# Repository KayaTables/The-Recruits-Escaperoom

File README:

Dit repository bevat de ontwerpfiles van de The Recruits escaperoom in Woerden (Bij HEL Shooter B.V.)

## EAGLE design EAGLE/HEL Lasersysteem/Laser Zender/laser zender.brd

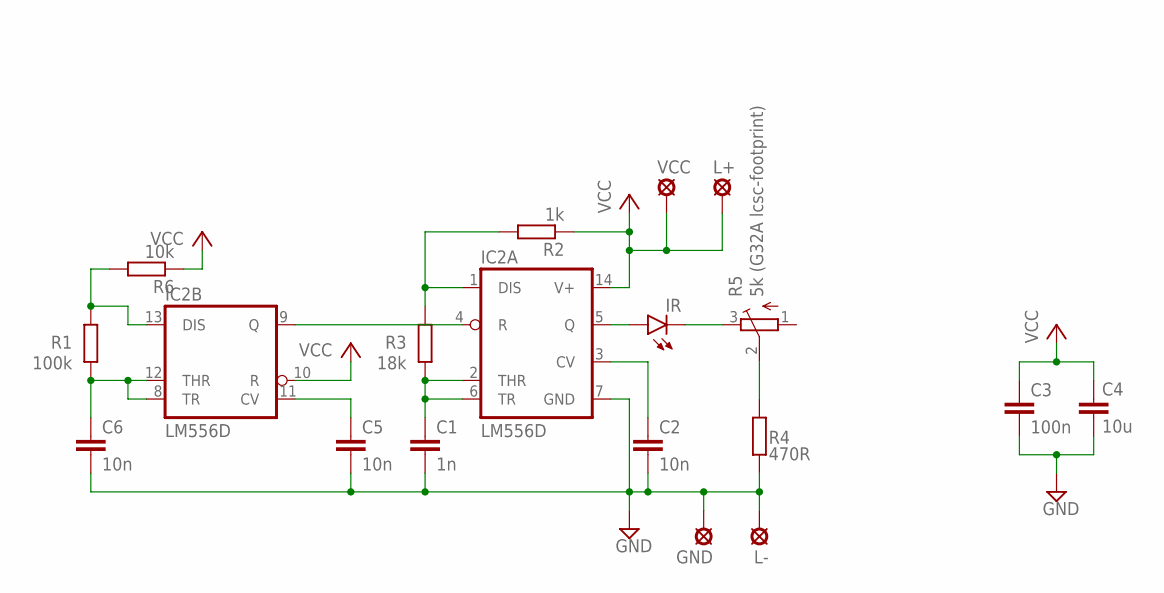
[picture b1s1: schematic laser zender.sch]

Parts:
C1: 1n; C0805
C2, C5, C6: 10n; C0805
C3: 100n; C0805
C4: 10u; C0805
GND: LSP10
IC2: LM556D; SO14
IR: LEDCHIPLED_0805; CHIPLED_0805
L+: LSP10
L-: LSP10
R1: 100k; R0805
R2: 1k; R0805
R3: 18k; R0805
R4: 470R; R0805
R5: 5k (G32A lcsc-footprint); 3223W
R6: 10k; R0805
VCC: LSP10

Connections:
GND: C1.2, C2.2, C3.2, C4.2, C5.2, C6.2, GND.MP, IC2.7 (GND), L-.MP, R4.2
unnamed: IR.C, R5.3 (E)
unnamed: C2.1, IC2.3 (CV)
unnamed: C1.1, IC2.2 (THR), IC2.6 (TR), R3.1
unnamed: R4.1, R5.2 (S)
unnamed: IC2.1 (DIS), R2.2, R3.2
unnamed: IC2.5 (Q), IR.A
unnamed: IC2.4 (R), IC2.9 (Q)
unnamed: IC2.13 (DIS), R1.2, R6.2
unnamed: C5.1, IC2.11 (CV)
unnamed: C6.1, IC2.8 (TR), IC2.12 (THR), R1.1
VCC: C3.1, C4.1, IC2.10 (R), IC2.14 (V+), L+.MP, R2.1, R6.1, VCC.MP

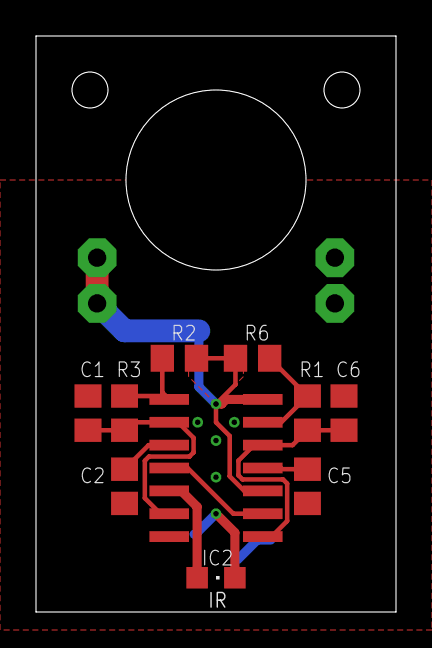
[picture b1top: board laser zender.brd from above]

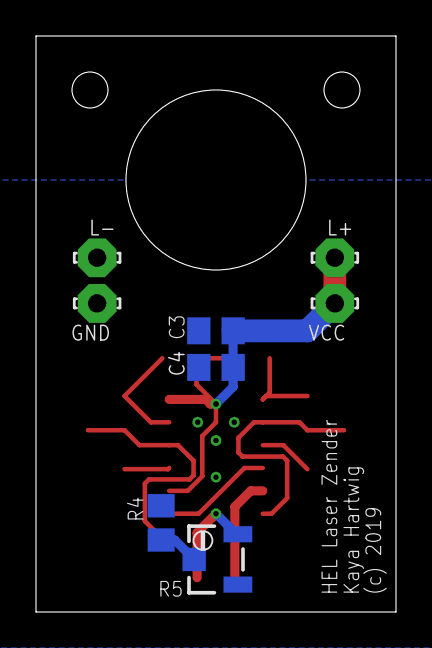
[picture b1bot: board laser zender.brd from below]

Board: 2 copper layers, 20.0 x 32.0 mm, 18 parts (8 on the bottom side), 12 nets.

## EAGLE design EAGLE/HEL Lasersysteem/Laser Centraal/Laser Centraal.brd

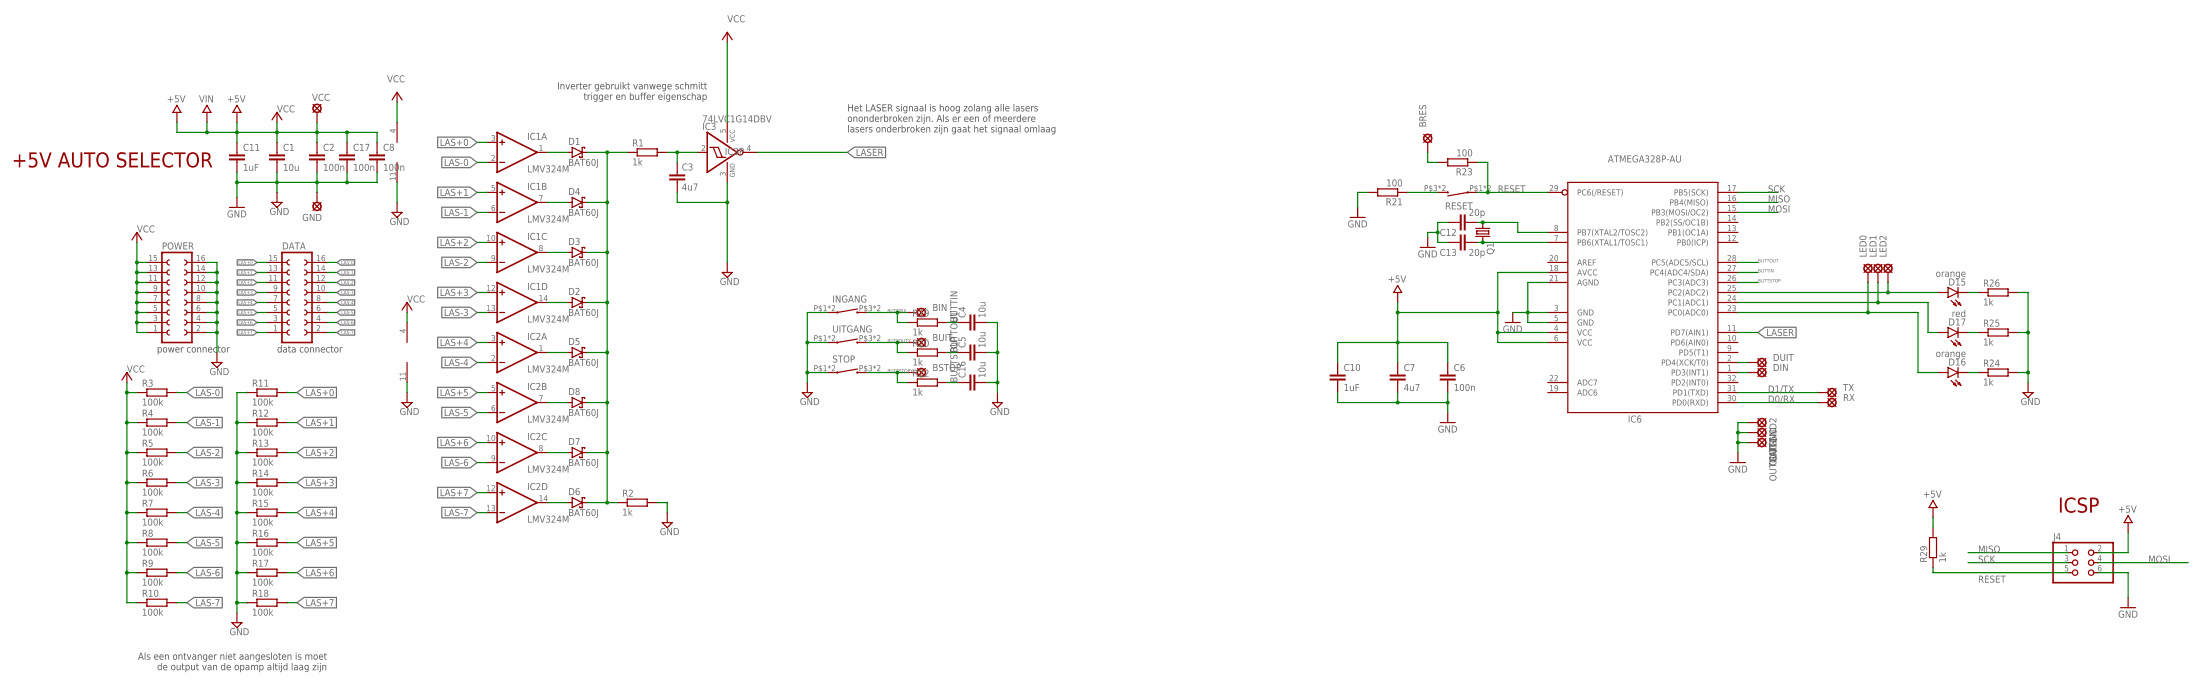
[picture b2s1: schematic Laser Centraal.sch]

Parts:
BIN: LSP10
BRES: LSP10
BSTOP: LSP10
BUIT: LSP10
C1, C4, C5, C16: 10u; C0805
C2, C6, C8, C17: 100n; C0805
C3, C7: 4u7; C0805
C10, C11: 1uF; C0805
C12, C13: 20p; C0805
D1, D2, D3, D4, D5, D6, D7, D8: BAT60J; SOD323_ST
D15, D16: orange; CHIP-LED0805
D17: red; CHIP-LED0805
DATA: FE08-2
DIN: LSP10
DUIT: LSP10
GND: LSP10
IC1, IC2: LMV324M; SO14
IC3: 74LVC1G14DBV; SOT23-5
IC6: ATMEGA328P-AU; TQFP32-08
INGANG: BRIGHTTSA061G100-250_SWITCH; BRIGHTTSA061G100-250
J4: 0114_PH254-203DF118A00V; 2X03
LED0, LED1, LED2: LSP10
OUTGND, OUTGND1, OUTGND2: LSP10
POWER: FE08-2
Q1: CRYSTALHC49U70; HC49U70
R1, R2, R19, R20, R22, R24, R25, R26, R29: 1k; R0805
R3, R4, R5, R6, R7, R8, R9, R10, R11, R12, R13, R14, R15, R16, R17, R18: 100k; R0805
R21, R23: 100; R0805
RESET: BRIGHTTSA061G100-250_SWITCH; BRIGHTTSA061G100-250
RX: LSP10
STOP: BRIGHTTSA061G100-250_SWITCH; BRIGHTTSA061G100-250
TX: LSP10
UITGANG: BRIGHTTSA061G100-250_SWITCH; BRIGHTTSA061G100-250
VCC: LSP10

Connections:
BUTTIN: C4.1, IC6.27 (PC4(ADC4/SDA)), R19.2
BUTTINX: BIN.MP, INGANG.P$3 (2), INGANG.P$4 (2), R19.1
BUTTOUT: C5.1, IC6.28 (PC5(ADC5/SCL)), R20.2
BUTTOUTX: BUIT.MP, R20.1, UITGANG.P$3 (2), UITGANG.P$4 (2)
BUTTSTOP: C16.1, IC6.26 (PC3(ADC3)), R22.2
BUTTSTOPX: BSTOP.MP, R22.1, STOP.P$3 (2), STOP.P$4 (2)
D0/RX: IC6.30 (PD0(RXD)), RX.MP
D1/TX: IC6.31 (PD1(TXD)), TX.MP
GND: C1.2, C2.2, C3.2, C4.2, C5.2, C6.2, C7.2, C8.2, C10.2, C11.2, C12.1, C13.1, C16.2, C17.2, GND.MP, IC1.11 (V-), IC2.11 (V-), IC3.3 (GND), IC6.3 (GND), IC6.5 (GND), IC6.21 (AGND), INGANG.P$1 (1), INGANG.P$2 (1), J4.6, OUTGND.MP, OUTGND1.MP, OUTGND2.MP, POWER.2, POWER.4, POWER.6, POWER.8, POWER.10, POWER.12, POWER.14, POWER.16, R2.2, R11.1, R12.1, R13.1, R14.1, R15.1, R16.1, R17.1, R18.1, R21.2, R24.2, R25.2, R26.2, STOP.P$1 (1), STOP.P$2 (1), UITGANG.P$1 (1), UITGANG.P$2 (1)
LAS+0: DATA.15, IC1.3 (+IN), R11.2
LAS+1: DATA.13, IC1.5 (+IN), R12.2
LAS+2: DATA.11, IC1.10 (+IN), R13.2
LAS+3: DATA.9, IC1.12 (+IN), R14.2
LAS+4: DATA.7, IC2.3 (+IN), R15.2
LAS+5: DATA.5, IC2.5 (+IN), R16.2
LAS+6: DATA.3, IC2.10 (+IN), R17.2
LAS+7: DATA.1, IC2.12 (+IN), R18.2
LAS-0: DATA.16, IC1.2 (-IN), R3.2
LAS-1: DATA.14, IC1.6 (-IN), R4.2
LAS-2: DATA.12, IC1.9 (-IN), R5.2
LAS-3: DATA.10, IC1.13 (-IN), R6.2
LAS-4: DATA.8, IC2.2 (-IN), R7.2
LAS-5: DATA.6, IC2.6 (-IN), R8.2
LAS-6: DATA.4, IC2.9 (-IN), R9.2
LAS-7: DATA.2, IC2.13 (-IN), R10.2
LASER: IC3.4 (O), IC6.11 (PD7(AIN1))
MISO: IC6.16 (PB4(MISO)), J4.1
MOSI: IC6.15 (PB3(MOSI/OC2)), J4.4
unnamed: D1.A, IC1.1 (OUT)
unnamed: D4.A, IC1.7 (OUT)
unnamed: D3.A, IC1.8 (OUT)
unnamed: D2.A, IC1.14 (OUT)
unnamed: D5.A, IC2.1 (OUT)
unnamed: D8.A, IC2.7 (OUT)
unnamed: D7.A, IC2.8 (OUT)
unnamed: D6.A, IC2.14 (OUT)
unnamed: D1.C, D2.C, D3.C, D4.C, D5.C, D6.C, D7.C, D8.C, R1.1, R2.1
unnamed: C3.1, IC3.2 (I), R1.2
unnamed: C13.2, IC6.7 (PB6(XTAL1/TOSC1)), Q1.2
unnamed: D16.C, R24.1
unnamed: D17.A, IC6.24 (PC1(ADC1)), LED1.MP
unnamed: D15.C, R26.1
unnamed: R21.1, RESET.P$3 (2), RESET.P$4 (2)
unnamed: D16.A, IC6.23 (PC0(ADC0)), LED0.MP
unnamed: C12.2, IC6.8 (PB7(XTAL2/TOSC2)), Q1.1
unnamed: BRES.MP, R23.2
unnamed: DUIT.MP, IC6.2 (PD4(XCK/T0))
unnamed: D17.C, R25.1
unnamed: D15.A, IC6.25 (PC2(ADC2)), LED2.MP
unnamed: DIN.MP, IC6.1 (PD3(INT1))
RESET: IC6.29 (PC6(/RESET)), J4.5, R23.1, R29.1, RESET.P$1 (1), RESET.P$2 (1)
SCK: IC6.17 (PB5(SCK)), J4.3
VCC: C1.1, C2.1, C6.1, C7.1, C8.1, C10.1, C11.1, C17.1, IC1.4 (V+), IC2.4 (V+), IC3.5 (VCC), IC6.4 (VCC), IC6.6 (VCC), IC6.18 (AVCC), J4.2, POWER.1, POWER.3, POWER.5, POWER.7, POWER.9, POWER.11, POWER.13, POWER.15, R3.1, R4.1, R5.1, R6.1, R7.1, R8.1, R9.1, R10.1, R29.2, VCC.MP

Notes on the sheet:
Inverter gebruikt vanwege schmitt trigger en buffer eigenschap
data connector
power connector
Als een ontvanger niet aangesloten is moet de output van de opamp altijd laag zijn
Het LASER signaal is hoog zolang alle lasers ononderbroken zijn. Als er een of meerdere lasers onderbroken zijn gaat het signaal omlaag
ICSP
+5V AUTO SELECTOR

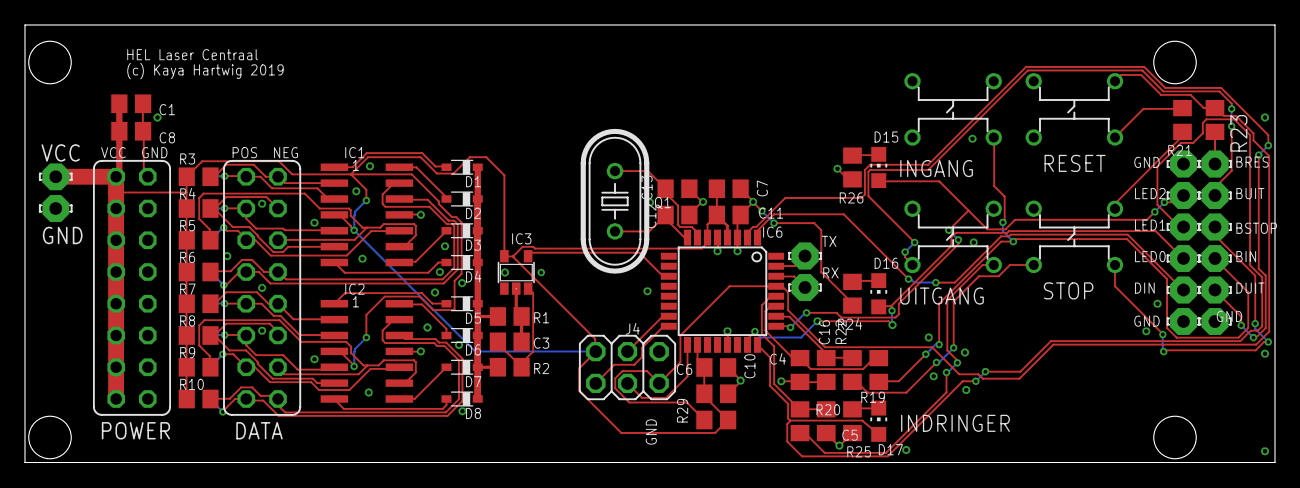
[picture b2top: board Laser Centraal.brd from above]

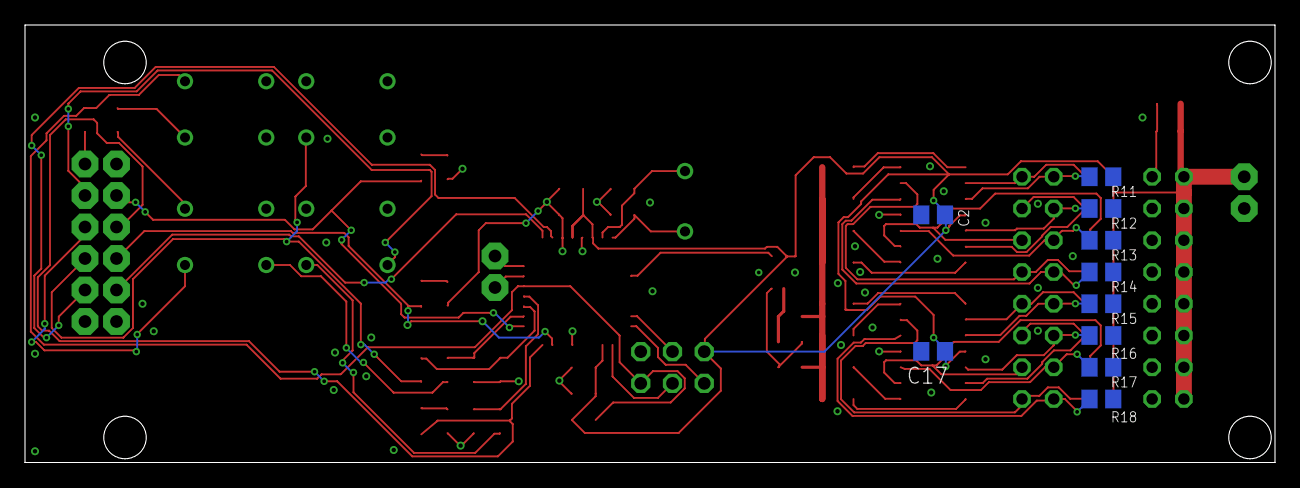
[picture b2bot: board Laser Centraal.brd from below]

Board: 2 copper layers, 100.0 x 35.0 mm, 80 parts (10 on the bottom side), 53 nets.

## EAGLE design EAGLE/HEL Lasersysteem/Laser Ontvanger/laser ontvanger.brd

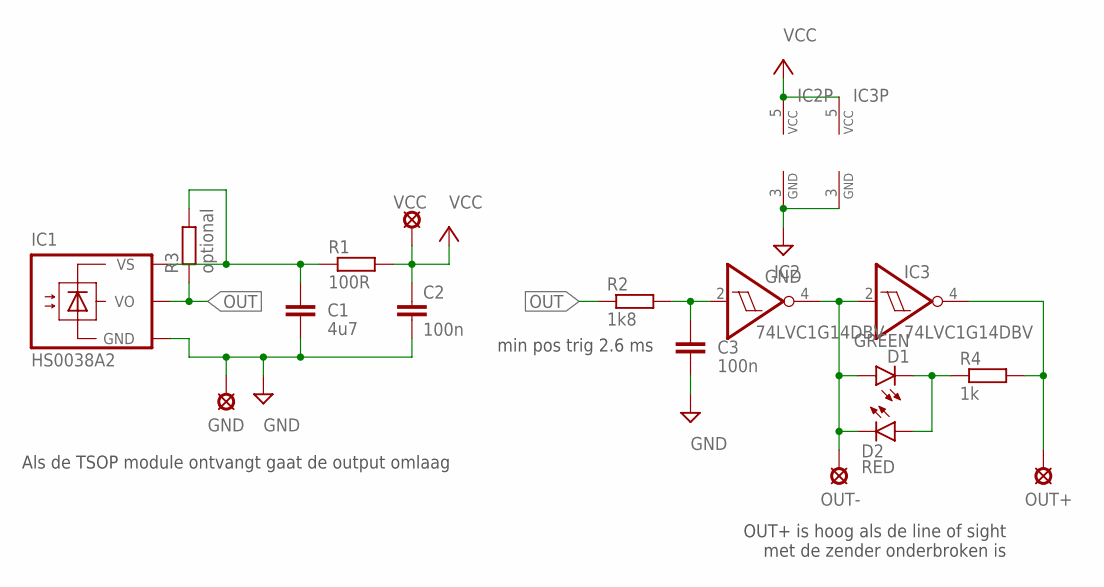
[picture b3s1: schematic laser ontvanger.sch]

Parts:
C1: 4u7; C0805
C2, C3: 100n; C0805
D1: GREEN; CHIP-LED0805
D2: RED; CHIP-LED0805
GND: LSP10
IC1: HS0038A2; TSOP17_TB1
IC2, IC3: 74LVC1G14DBV; SOT23-5
OUT+: LSP10
OUT-: LSP10
R1: 100R; R0805
R2: 1k8; R0805
R3: optional; R0805
R4: 1k; R0805
VCC: LSP10

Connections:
GND: C1.2, C2.2, C3.2, GND.MP, IC1.GND, IC2.3 (GND), IC3.3 (GND)
unnamed: C3.1, IC2.2 (I), R2.2
unnamed: D1.C, D2.A, R4.1
unnamed: D1.A, D2.C, IC2.4 (O), IC3.2 (I), OUT-.MP
unnamed: IC3.4 (O), OUT+.MP, R4.2
unnamed: C1.1, IC1.VS, R1.1, R3.2
OUT: IC1.VO, R2.1, R3.1
VCC: C2.1, IC2.5 (VCC), IC3.5 (VCC), R1.2, VCC.MP

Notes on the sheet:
Als de TSOP module ontvangt gaat de output omlaag
min pos trig 2.6 ms
OUT+ is hoog als de line of sight met de zender onderbroken is

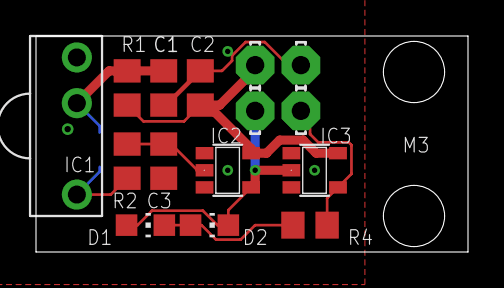
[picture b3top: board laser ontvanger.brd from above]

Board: 2 copper layers, 24.0 x 12.0 mm, 16 parts (1 on the bottom side), 8 nets.

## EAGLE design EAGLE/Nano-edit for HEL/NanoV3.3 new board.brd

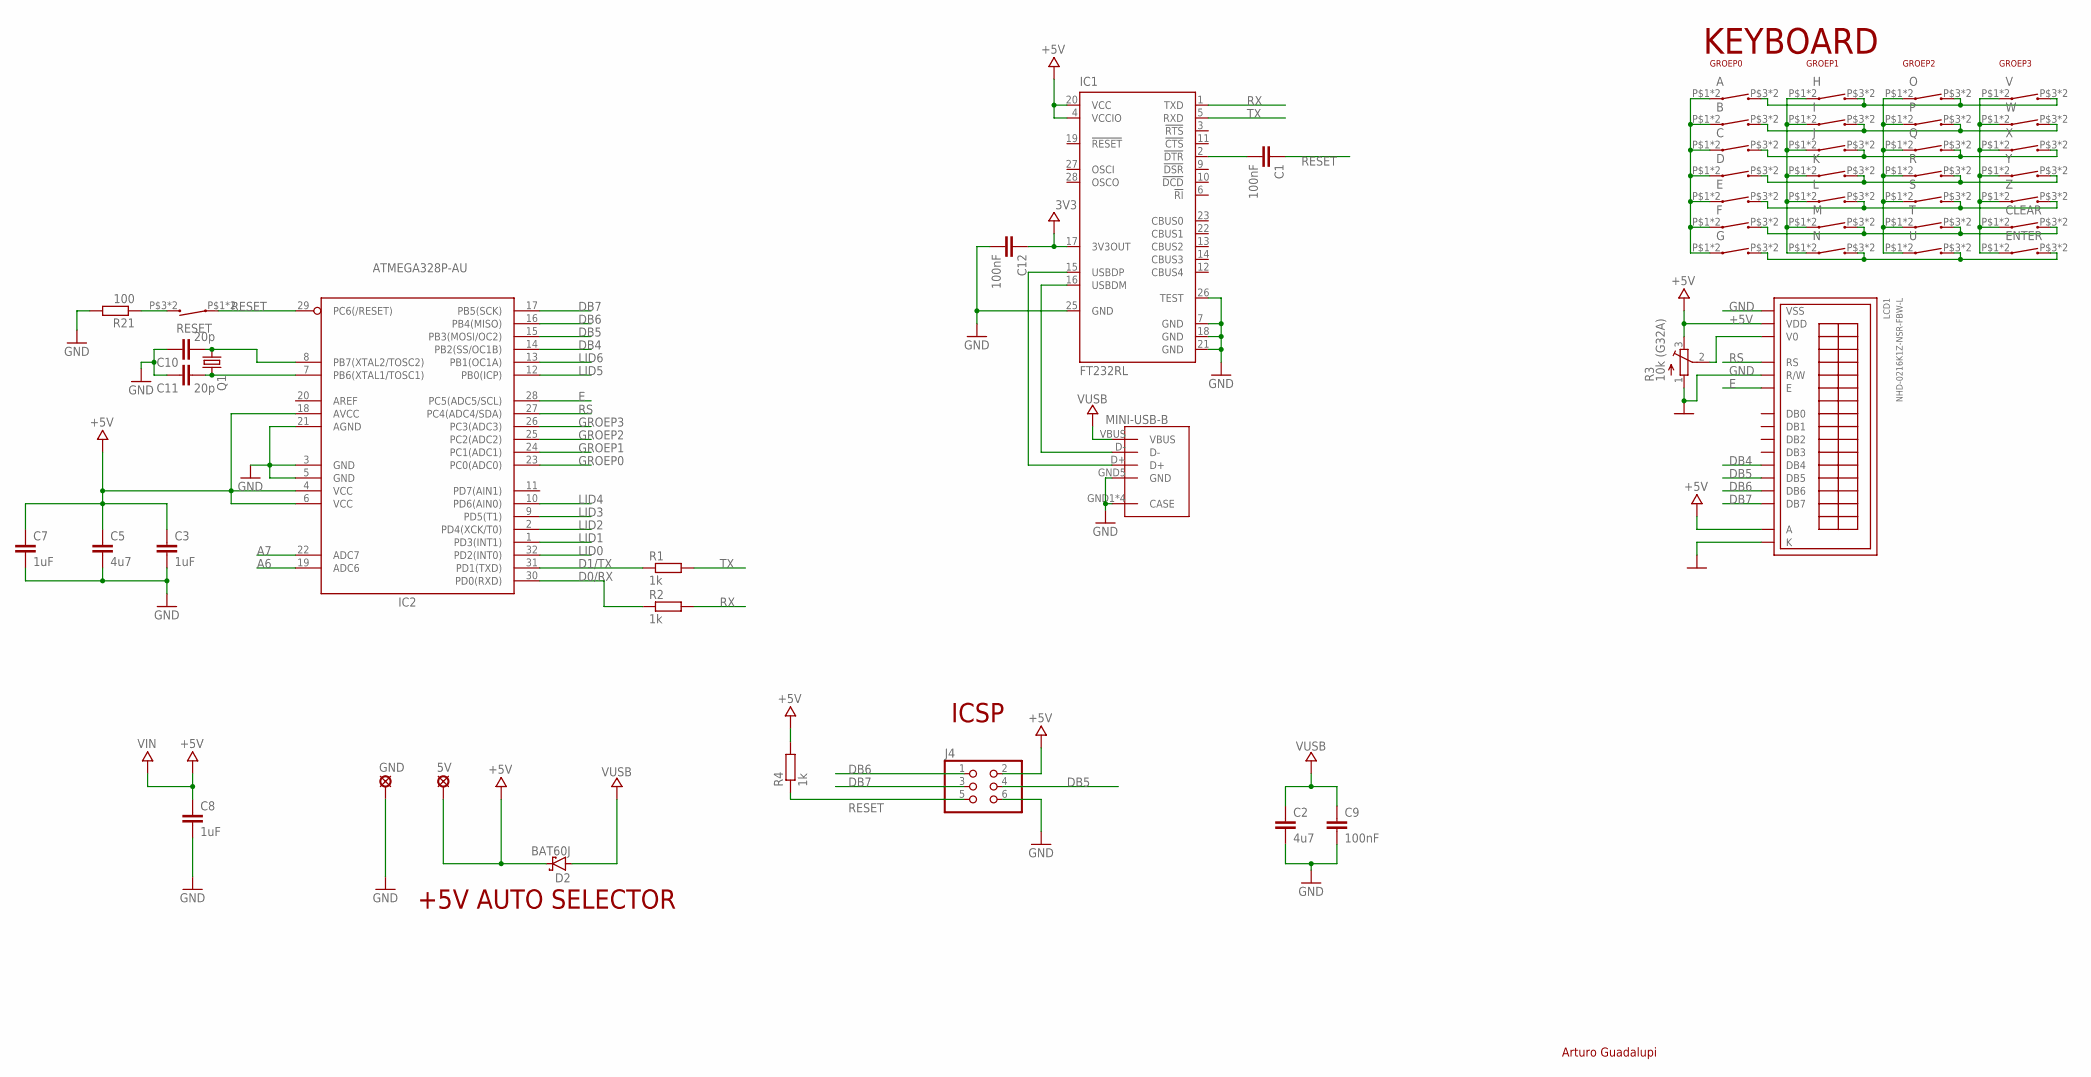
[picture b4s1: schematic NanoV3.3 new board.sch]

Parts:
5V: LSP10
A: BRIGHTTSA061G100-250_SWITCH; BRIGHTTSA061G100-250
B: BRIGHTTSA061G100-250_SWITCH; BRIGHTTSA061G100-250
C: BRIGHTTSA061G100-250_SWITCH; BRIGHTTSA061G100-250
C1, C9, C12: 100nF; C0805
C2, C5: 4u7; C0805
C3, C7, C8: 1uF; C0805
C10, C11: 20p; C0805
CLEAR: BRIGHTTSA061G100-250_SWITCH; BRIGHTTSA061G100-250
D: BRIGHTTSA061G100-250_SWITCH; BRIGHTTSA061G100-250
D2: BAT60J; SOD323_ST
E: BRIGHTTSA061G100-250_SWITCH; BRIGHTTSA061G100-250
ENTER: BRIGHTTSA061G100-250_SWITCH; BRIGHTTSA061G100-250
F: BRIGHTTSA061G100-250_SWITCH; BRIGHTTSA061G100-250
G: BRIGHTTSA061G100-250_SWITCH; BRIGHTTSA061G100-250
GND: LSP10
H: BRIGHTTSA061G100-250_SWITCH; BRIGHTTSA061G100-250
I: BRIGHTTSA061G100-250_SWITCH; BRIGHTTSA061G100-250
IC1: FT232RL; SSOP28
IC2: ATMEGA328P-AU; TQFP32-08
J: BRIGHTTSA061G100-250_SWITCH; BRIGHTTSA061G100-250
J4: 0114_PH254-203DF118A00V; 2X03
K: BRIGHTTSA061G100-250_SWITCH; BRIGHTTSA061G100-250
L: BRIGHTTSA061G100-250_SWITCH; BRIGHTTSA061G100-250
LCD1: NHD-0216K1Z-NSR-FBW-L; LCD_NO-HEAD
M: BRIGHTTSA061G100-250_SWITCH; BRIGHTTSA061G100-250
MINI-USB-B: MINI_USB_B-KRHRO-SELECU-M-M5DS-W-4; KRHROSELECU-M-M5DS-W-4
N: BRIGHTTSA061G100-250_SWITCH; BRIGHTTSA061G100-250
O: BRIGHTTSA061G100-250_SWITCH; BRIGHTTSA061G100-250
P: BRIGHTTSA061G100-250_SWITCH; BRIGHTTSA061G100-250
Q: BRIGHTTSA061G100-250_SWITCH; BRIGHTTSA061G100-250
Q1: CRYSTALHC49U70; HC49U70
R: BRIGHTTSA061G100-250_SWITCH; BRIGHTTSA061G100-250
R1, R2, R4: 1k; R0805
R3: 10k (G32A); 3223W
R21: 100; R0805
RESET: BRIGHTTSA061G100-250_SWITCH; BRIGHTTSA061G100-250
S: BRIGHTTSA061G100-250_SWITCH; BRIGHTTSA061G100-250
T: BRIGHTTSA061G100-250_SWITCH; BRIGHTTSA061G100-250
U: BRIGHTTSA061G100-250_SWITCH; BRIGHTTSA061G100-250
V: BRIGHTTSA061G100-250_SWITCH; BRIGHTTSA061G100-250
W: BRIGHTTSA061G100-250_SWITCH; BRIGHTTSA061G100-250
X: BRIGHTTSA061G100-250_SWITCH; BRIGHTTSA061G100-250
Y: BRIGHTTSA061G100-250_SWITCH; BRIGHTTSA061G100-250
Z: BRIGHTTSA061G100-250_SWITCH; BRIGHTTSA061G100-250

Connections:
3V3: C12.1, IC1.17 (3V3OUT)
+5V: 5V.MP, C3.1, C5.1, C7.1, C8.1, D2.C, IC1.4 (VCCIO), IC1.20 (VCC), IC2.4 (VCC), IC2.6 (VCC), IC2.18 (AVCC), J4.2, LCD1.2 (VDD), LCD1.15 (A), R3.3 (E), R4.2
A6: IC2.19 (ADC6)
A7: IC2.22 (ADC7)
D0/RX: IC2.30 (PD0(RXD)), R2.1
D1/TX: IC2.31 (PD1(TXD)), R1.1
DB4: IC2.14 (PB2(SS/OC1B)), LCD1.11 (DB4)
DB5: IC2.15 (PB3(MOSI/OC2)), J4.4, LCD1.12 (DB5)
DB6: IC2.16 (PB4(MISO)), J4.1, LCD1.13 (DB6)
DB7: IC2.17 (PB5(SCK)), J4.3, LCD1.14 (DB7)
E: IC2.28 (PC5(ADC5/SCL)), LCD1.6 (E)
GND: C2.2, C3.2, C5.2, C7.2, C8.2, C9.2, C10.1, C11.1, C12.2, GND.MP, IC1.7 (GND), IC1.18 (GND), IC1.21 (GND), IC1.25 (GND), IC1.26 (TEST), IC2.3 (GND), IC2.5 (GND), IC2.21 (AGND), J4.6, LCD1.1 (VSS), LCD1.5 (R/W), LCD1.16 (K), MINI-USB-B.GND1 (CASE), MINI-USB-B.GND2 (CASE), MINI-USB-B.GND3 (CASE), MINI-USB-B.GND4 (CASE), MINI-USB-B.GND5 (GND), R3.1 (A), R21.2
GROEP0: A.P$1 (1), A.P$2 (1), B.P$1 (1), B.P$2 (1), C.P$1 (1), C.P$2 (1), D.P$1 (1), D.P$2 (1), E.P$1 (1), E.P$2 (1), F.P$1 (1), F.P$2 (1), G.P$1 (1), G.P$2 (1), IC2.23 (PC0(ADC0))
GROEP1: H.P$1 (1), H.P$2 (1), I.P$1 (1), I.P$2 (1), IC2.24 (PC1(ADC1)), J.P$1 (1), J.P$2 (1), K.P$1 (1), K.P$2 (1), L.P$1 (1), L.P$2 (1), M.P$1 (1), M.P$2 (1), N.P$1 (1), N.P$2 (1)
GROEP2: IC2.25 (PC2(ADC2)), O.P$1 (1), O.P$2 (1), P.P$1 (1), P.P$2 (1), Q.P$1 (1), Q.P$2 (1), R.P$1 (1), R.P$2 (1), S.P$1 (1), S.P$2 (1), T.P$1 (1), T.P$2 (1), U.P$1 (1), U.P$2 (1)
GROEP3: CLEAR.P$1 (1), CLEAR.P$2 (1), ENTER.P$1 (1), ENTER.P$2 (1), IC2.26 (PC3(ADC3)), V.P$1 (1), V.P$2 (1), W.P$1 (1), W.P$2 (1), X.P$1 (1), X.P$2 (1), Y.P$1 (1), Y.P$2 (1), Z.P$1 (1), Z.P$2 (1)
LID0: A.P$3 (2), A.P$4 (2), H.P$3 (2), H.P$4 (2), IC2.32 (PD2(INT0)), O.P$3 (2), O.P$4 (2), V.P$3 (2), V.P$4 (2)
LID1: B.P$3 (2), B.P$4 (2), I.P$3 (2), I.P$4 (2), IC2.1 (PD3(INT1)), P.P$3 (2), P.P$4 (2), W.P$3 (2), W.P$4 (2)
LID2: C.P$3 (2), C.P$4 (2), IC2.2 (PD4(XCK/T0)), J.P$3 (2), J.P$4 (2), Q.P$3 (2), Q.P$4 (2), X.P$3 (2), X.P$4 (2)
LID3: D.P$3 (2), D.P$4 (2), IC2.9 (PD5(T1)), K.P$3 (2), K.P$4 (2), R.P$3 (2), R.P$4 (2), Y.P$3 (2), Y.P$4 (2)
LID4: E.P$3 (2), E.P$4 (2), IC2.10 (PD6(AIN0)), L.P$3 (2), L.P$4 (2), S.P$3 (2), S.P$4 (2), Z.P$3 (2), Z.P$4 (2)
LID5: CLEAR.P$3 (2), CLEAR.P$4 (2), F.P$3 (2), F.P$4 (2), IC2.12 (PB0(ICP)), M.P$3 (2), M.P$4 (2), T.P$3 (2), T.P$4 (2)
LID6: ENTER.P$3 (2), ENTER.P$4 (2), G.P$3 (2), G.P$4 (2), IC2.13 (PB1(OC1A)), N.P$3 (2), N.P$4 (2), U.P$3 (2), U.P$4 (2)
unnamed: C10.2, IC2.8 (PB7(XTAL2/TOSC2)), Q1.1
unnamed: C11.2, IC2.7 (PB6(XTAL1/TOSC1)), Q1.2
unnamed: LCD1.3 (V0), R3.2 (S)
unnamed: IC1.15 (USBDP), MINI-USB-B.D+
unnamed: IC1.16 (USBDM), MINI-USB-B.D-
unnamed: C1.2, IC1.2 (!DTR)
unnamed: R21.1, RESET.P$3 (2), RESET.P$4 (2)
RESET: C1.1, IC2.29 (PC6(/RESET)), J4.5, R4.1, RESET.P$1 (1), RESET.P$2 (1)
RS: IC2.27 (PC4(ADC4/SDA)), LCD1.4 (RS)
RX: IC1.1 (TXD), R2.2
TX: IC1.5 (RXD), R1.2
VUSB: C2.1, C9.1, D2.A, MINI-USB-B.VBUS

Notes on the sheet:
ICSP
+5V AUTO SELECTOR
Arturo Guadalupi
KEYBOARD
GROEP0
GROEP1
GROEP2
GROEP3

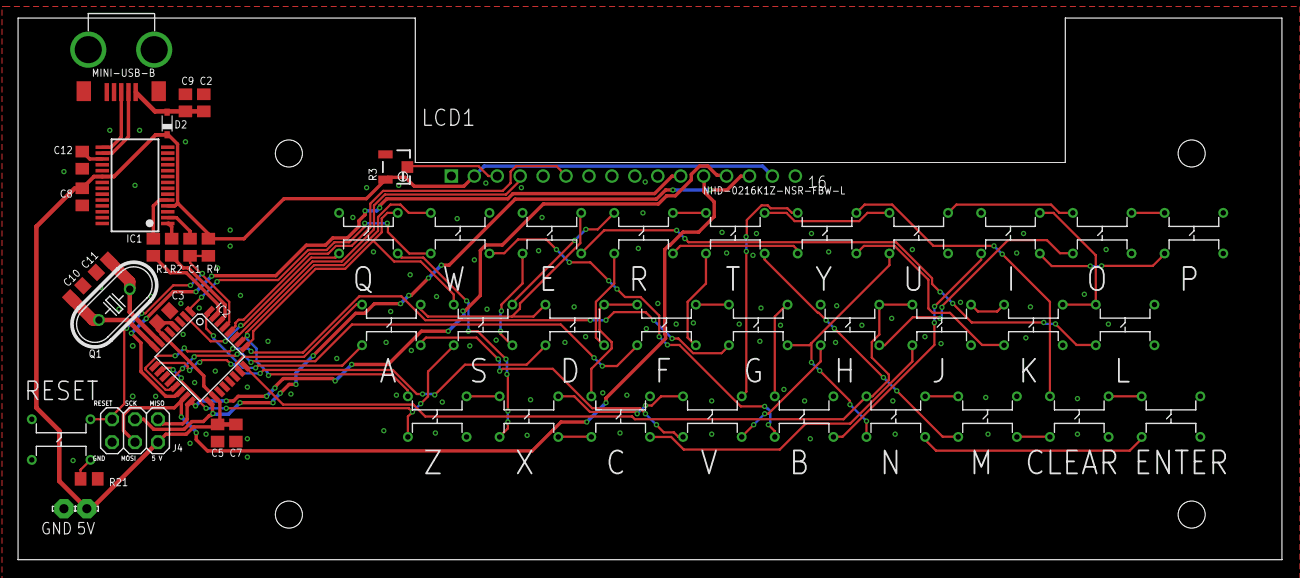
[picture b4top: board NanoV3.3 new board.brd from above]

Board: 2 copper layers, 140.0 x 60.0 mm, 53 parts (0 on the bottom side), 33 nets.

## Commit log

2019-05-05 gitattributes gemaakt
2019-05-05 gitattributes verbeterd
2019-05-05 ik hoop dat de attributes file het nu wel doet :b
2019-05-05 bestaande files toegevoegd
2019-05-05 Laser PCB's aangepast
2019-05-12 tweede versie laser gerbers klaargemaakt voor bestelling
2019-05-19 vergeten bestandjes toegevoegd
2019-05-26 begin gemaakt analyse microfoon en vergeten gerbers toegevoegd
2019-05-26 nodeloze files verwijderd en to do aangepast
2019-05-26 documententatie rond computerpuzzel duidelijker gemaakt
2019-05-29 ontvanger/zender partslists naar versie twee
2019-05-29 kleine aanpassingen
2019-06-25 onedrive gaat niet lekker samen met git. hopelijk levert het geen problemen op
2019-06-25 alarm escaperoom uitgezet
2019-06-25 takenlijstje aangevuld
2019-06-28 pdf gemaakt van laser centraal
2019-07-03 ik probeer de laser centrale aan de praat te krijgen
2019-09-01 lang vergeten te comitten. Er is oa een HEL raspberry bij gekomen

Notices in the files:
EAGLE/HEL Lasersysteem/Laser Ontvanger/laser ontvanger.brd:
(c) 2019
parts and their libraries:
Arduino-ucs: Copyright (c) 2016-2017 Arduino LLC.  All right reserved.
